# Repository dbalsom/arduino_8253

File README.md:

# Arduino8253

This project defines an Arduino interface to the Intel 8253 PIT.

## Why?

To more deeply investigate the behavior of this chip to enable more accurate emulation for my emulator [MartyPC](https://dbalsom.github.io/martypc/)

## Details

This project utilizes an Arduino UNO R3 or compatible clone. The included Arduino sketch includes a test suite and PIT emulator. These were developed together. 
Results of the test are compared to the emulated results to ensure the emulator is accurate. The PIT emulator was used as the basis for a new PIT emulation implementation
in MartyPC which improved timings and fixed PCM audio playback.

Fritzing and KiCad projects are supplied. This project never moved beyond the breadboard stage, so no PCB is defined in the KiCad project. Feel free to add one.
The Fritzing project shows the breadboard layout with some additional functionality - the output lines are tied to status LEDs, and a hex inverter and octal latch 
are used to capture the data lines from the PIT and display them using LEDs. 

## 8254

This same project can be used to investigate the 8254, which is pin-compatible. The main differences between the 8253 and 8254 are that the 8524 added the read-back command
and enables interleaved reads and writes per timer channel in LSBMSB mode. 

## License

This project is MIT licensed.

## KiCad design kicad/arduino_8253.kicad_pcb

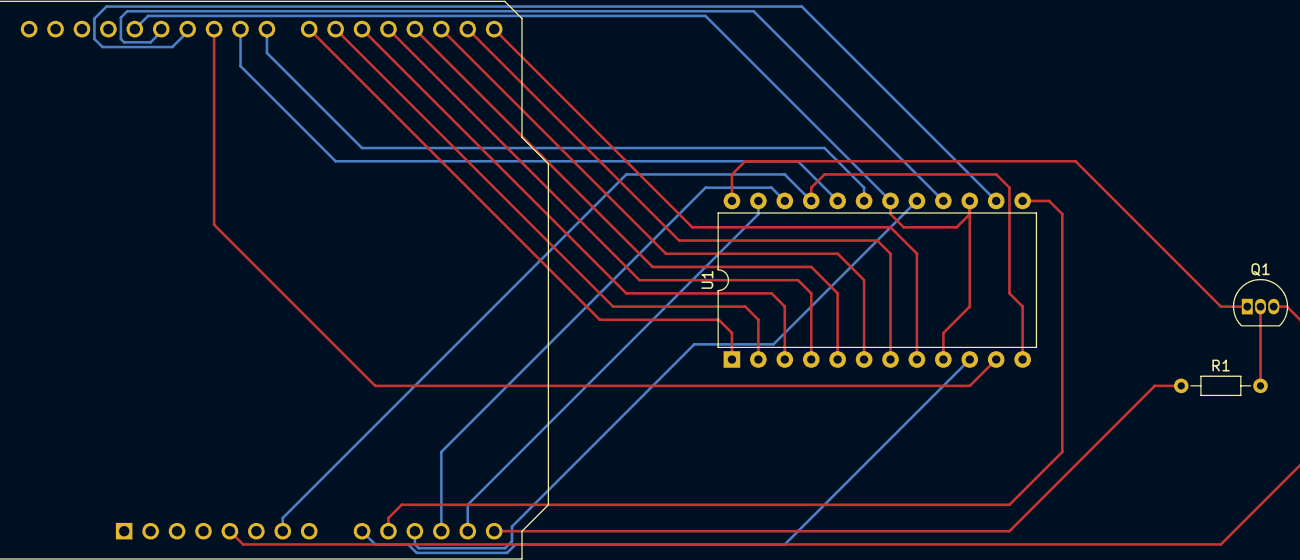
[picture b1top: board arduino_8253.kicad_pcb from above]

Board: 2 copper layers, 4 parts (0 on the bottom side), 24 nets.

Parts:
A1: Arduino_UNO_R3
Q1: 2N3904; TO-92_Inline
R1: 1k; R_Axial_DIN0204_L3.6mm_D1.6mm_P7.62mm_Horizontal
U1: 8253; DIP-24_W15.24mm

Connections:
+5V: A1.5 (+5V), Q1.3 (C)
/D0: A1.15 (D0/RX), U1.8 (D0)
/D1: A1.16 (D1/TX), U1.7 (D1)
/D2: A1.17 (D2), U1.6 (D2)
/D3: A1.18 (D3), U1.5 (D3)
/D4: A1.19 (D4), U1.4 (D4)
/D5: A1.20 (D5), U1.3 (D5)
/D6: A1.21 (D6), U1.2 (D6)
/D7: A1.22 (D7), U1.1 (D7)
A0: A1.23 (D8), U1.19 (A0)
A1: A1.24 (D9), U1.20 (A1)
CLK: A1.28 (D13), U1.9 (CLK0), U1.15 (CLK1), U1.18 (CLK2)
G0: A1.25 (D10), U1.11 (G0)
G1: A1.26 (D11), U1.14 (G1)
G2: A1.27 (D12), U1.16 (G2)
GND: A1.7 (GND), U1.12 (GND), U1.21 (~CS)
unnamed: A1.14 (SCL/A5), R1.1
unnamed: Q1.2 (B), R1.2
unnamed: Q1.1 (E), U1.24 (VCC)
OUT0: A1.9 (A0), U1.10 (OUT0)
OUT1: A1.10 (A1), U1.13 (OUT1)
OUT2: A1.11 (A2), U1.17 (OUT2)
~RD: A1.12 (A3), U1.22 (~RD)
~WR: A1.13 (SDA/A4), U1.23 (~WR)

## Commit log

2023-07-18 Add LICENSE
2023-07-18 Remove old sketch directory
2023-07-18 Move sketch files down one directory
